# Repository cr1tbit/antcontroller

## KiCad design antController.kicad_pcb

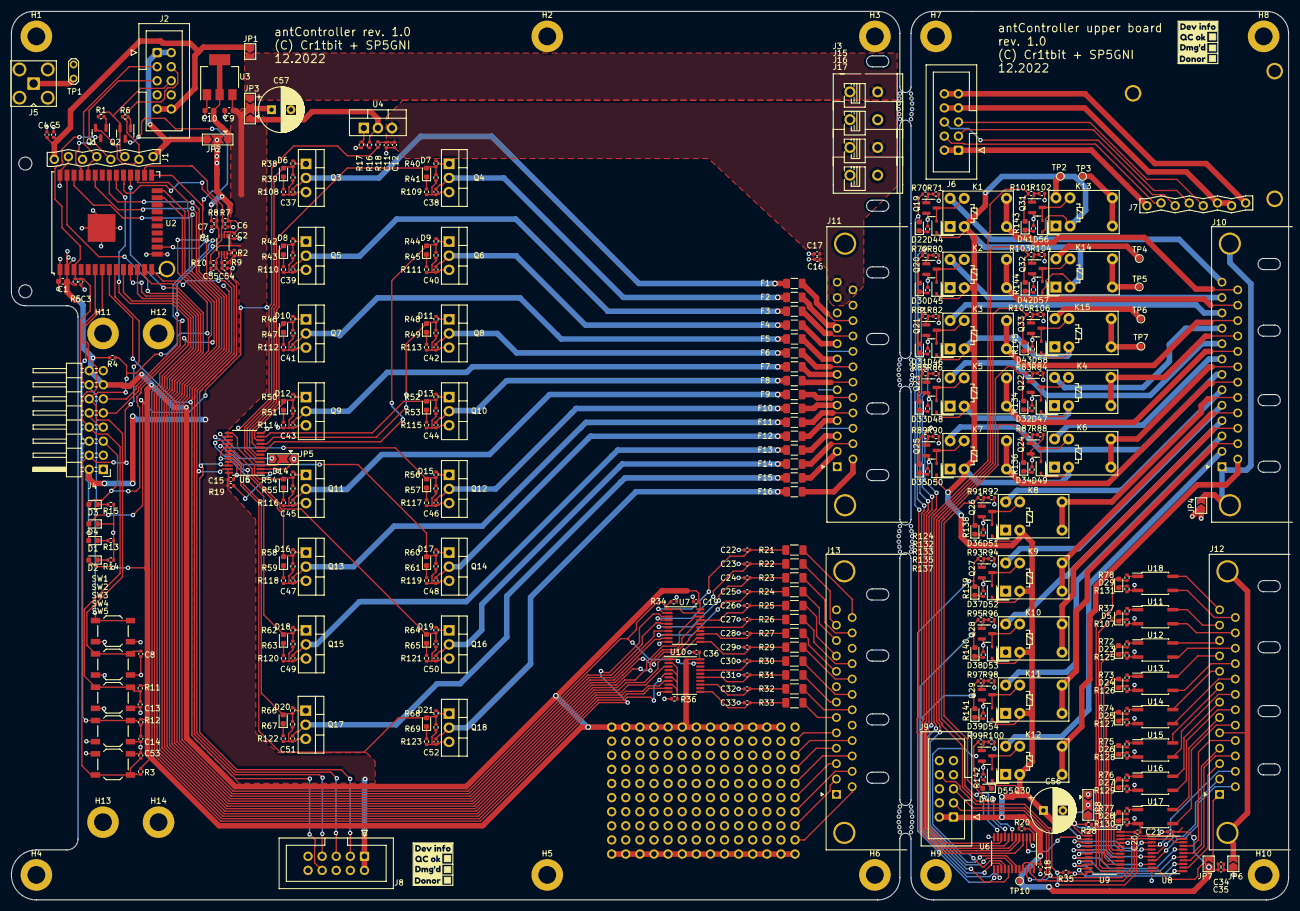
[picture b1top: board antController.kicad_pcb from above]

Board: 2 copper layers, 230.0 x 160.0 mm, 402 parts (0 on the bottom side), 326 nets.

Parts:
C1, C9, C10: 10u; C_0603_1608Metric
C2, C3, C4, C8, C11, C13, C14, C15, C16, C18, C19, C20, C21, C34, C36, C53: 100n; C_0402_1005Metric
C5, C12, C17, C35: 1n; C_0402_1005Metric
C6, C7, C54, C55: 1n/DNP; C_0402_1005Metric
C22, C23, C24, C25, C26, C27, C28, C29, C30, C31, C32, C33, C37, C38, C39, C40, C41, C42, C43, C44, C45, C46, C47, C48, C49, C50, C51, C52: 10n; C_0402_1005Metric
C56, C57: 220u; CP_Radial_D8.0mm_P3.50mm
D1, D2, D3, D4, D5, D6, D7, D8, D9, D10, D11, D12, D13, D14, D15, D16, D17, D18, D19, D20, D21, D22, D23, D24, D25, D26, D27, D28, D29, D30, D31, D32, D33, D34, D35, D36, D37, D38, D39, D40, D41, D42, D43: LED_RED; LED_0603_1608Metric
D44, D45, D46, D47, D48, D49, D50, D51, D52, D53, D54, D55, D56, D57, D58: 1N4148WS; D_SOD-323
F1, F2, F3, F4, F5, F6, F7, F8, F9, F10, F11, F12, F13, F14, F15, F16: FUSE_1206; Fuse_1206_3216Metric
H1, H2, H3, H4, H5, H6, H11, H12, H13, H14: SCRHOLE; MountingHole_3.2mm_M3_ISO7380_Pad
H7, H8, H9, H10: HOLE_B2; MountingHole_3.2mm_M3_ISO7380_Pad
J1, J7: Lichtenprog_conn; Lichtenprog_board
J2, J6, J8, J9: IDC10; IDC-Header_2x05_P2.54mm_Vertical
J3, J15, J16, J17: VIN; DG235-5.0
J4: FRONT_PANEL; PinHeader_2x08_P2.54mm_Horizontal
J5: SMA CONN; SMA_Amphenol_901-143_Horizontal
J10, J11, J12, J13: DB25_Male_MountingHoles; DSUB-25_Male_Horizontal_P2.77x2.84mm_EdgePinOffset9.90mm_Ho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
J14: Proto_matrix_14x10
JP1: 5V_PROG; SolderJumper-2_P1.3mm_Open_TrianglePad1.0x1.5mm
JP2: 3V3_SEL; SolderJumper-3_P2.0mm_Open_TrianglePad1.0x1.5mm
JP3: 5V_SEL; SolderJumper-3_P2.0mm_Open_TrianglePad1.0x1.5mm
JP4, JP6: GND_CONN; SolderJumper-2_P1.3mm_Open_TrianglePad1.0x1.5mm
JP5, JP8: IOEX_A2_SEL; SolderJumper-3_P2.0mm_Open_TrianglePad1.0x1.5mm
JP7: 5V_CONN; SolderJumper-2_P1.3mm_Open_TrianglePad1.0x1.5mm
K1, K2, K3, K4, K5, K6, K7, K8, K9, K10, K11, K12, K13, K14, K15: G5V-1; Relay_SPDT_Omron_G5V-1
Q1, Q2, Q19, Q20, Q21, Q22, Q23, Q24, Q25, Q26, Q27, Q28, Q29, Q30, Q31, Q32, Q33: MMBT3904; SOT-23
Q3, Q4, Q5, Q6, Q7, Q8, Q9, Q10, Q11, Q12, Q13, Q14, Q15, Q16, Q17, Q18: BUZ11; TO-220-3_Vertical
R1, R3, R4, R5, R6, R11, R12, R19, R20, R28, R34, R35, R36, R39, R41, R43, R45, R47, R49, R51, R53, R55, R57, R59, R61, R63, R65, R67, R69, R71, R80, R82, R84, R86, R88, R90, R92, R94, R96, R98, R100, R102, R104, R106: 10k; R_0402_1005Metric
R2: 200k; R_0402_1005Metric
R7, R8, R9, R10, R37, R38, R40, R42, R44, R46, R48, R50, R52, R54, R56, R58, R60, R62, R64, R66, R68, R70, R72, R73, R74, R75, R76, R77, R78, R79, R81, R83, R85, R87, R89, R91, R93, R95, R97, R99, R101, R103, R105: 4k7; R_0402_1005Metric
R13, R107, R108, R109, R110, R111, R112, R113, R114, R115, R116, R117, R118, R119, R120, R121, R122, R123, R124, R125, R126, R127, R128, R129, R130, R131, R132, R133, R134, R135, R136, R137, R138, R139, R140, R141, R142, R143, R144, R145: 33k; R_0402_1005Metric
R14, R15: 15k; R_0402_1005Metric
R16: 240; R_0402_1005Metric
R17: 720; R_0402_1005Metric
R18: 100k; R_0402_1005Metric
R21, R22, R23, R24, R25, R26, R27, R29, R30, R31, R32, R33: 10k_1206; R_1206_3216Metric_Pad1.30x1.75mm_HandSolder
SW1: B_RST; SW_SPST_TL3342
SW2: B1/BOOT; SW_SPST_TL3342
SW3: B2; SW_SPST_TL3342
SW4, SW5: B3; SW_SPST_TL3342
TP1: SMA PADS; TestPoint_2Pads_Pitch2.54mm_Drill0.8mm
TP2, TP3, TP4, TP5, TP6, TP7: RLPAD; TestPoint_Pad_D1.0mm
TP10: IOPAD; TestPoint_Pad_D1.0mm
U1: PCA9306DC; VSSOP-8_2.3x2mm_P0.5mm
U2: ESP32-WROOM-32U
U3: AZ1117-3.3; SOT-223-3_TabPin2
U4: LM317_TO-220; TO-220-3_Vertical
U5, U6, U9: PCA9555PW; TSSOP-24_4.4x7.8mm_P0.65mm
U7, U8, U10: 74HC244; TSSOP-20_4.4x6.5mm_P0.65mm
U11, U12, U13, U14, U15, U16, U17, U18: LTV-356T; SO-4_4.4x3.6mm_P2.54mm
kibuzzard-6394C46A, kibuzzard-6394C46A#2: G***; kibuzzard-6394C46A
kibuzzard-6394C47E, kibuzzard-6394C47E#2: G***; kibuzzard-6394C47E
kibuzzard-6394C445, kibuzzard-6394C445#2: G***; kibuzzard-6394C445
kibuzzard-6394C560, kibuzzard-6394C560#2: G***; kibuzzard-6394C560

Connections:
+3.3V: C1.1, C2.1, C19.1, C36.1, D2.2 (A), J4.13, J4.16, J14.A2, J14.A3, J14.A4, J14.A5, J14.A6, J14.A7, J14.A8, J14.A9, J14.A10, J14.A11, J14.A12, J14.A13, J14.A14, JP2.2 (C), R3.2, R4.2, R5.2, R7.2, R8.2, R11.2, R12.2, U1.2 (VREF1), U2.2 (VDD), U7.20 (VCC), U10.20 (VCC)
+5V: C9.1, C15.1, C57.1, D1.2 (A), J4.2, J8.1, J8.2, JP3.2 (C), JP5.3 (B), R2.2, R9.2, R10.2, R19.2, U3.3 (VI), U5.24 (VDD)
+5VD: C18.1, C20.1, C21.1, C34.2, C35.2, C56.1, D44.1 (K), D45.1 (K), D46.1 (K), D47.1 (K), D48.1 (K), D49.1 (K), D50.1 (K), D51.1 (K), D52.1 (K), D53.1 (K), D54.1 (K), D55.1 (K), D56.1 (K), D57.1 (K), D58.1 (K), J9.1, J9.2, JP7.1 (A), JP8.3 (B), K1.2, K2.2, K3.2, K4.2, K5.2, K6.2, K7.2, K8.2, K9.2, K10.2, K11.2, K12.2, K13.2, K14.2, K15.2, R20.2, R28.2, U6.21 (A0), U6.24 (VDD), U8.20 (VCC), U9.2 (A1), U9.24 (VDD)
+VDC: C11.1, C12.1, C16.1, C17.1, J11.12, J11.13, J11.25, J16.1, R18.2, U4.3 (VI)
/5V_IN: J3.1, JP1.2 (B), JP3.3 (B)
/B2: C13.1, J4.8, R11.1, SW3.2, U2.7 (IO35)
/B3: C14.1, J4.6, R12.1, SW4.2, U2.6 (IO34)
/B4: C53.1, J4.4, R3.1, SW5.2, U2.9 (IO33)
/Back connectors/B2_OUT_BUF_ENA: J9.8, R35.2, U8.1 (1OE), U8.19 (2OE)
/Back connectors/B2_PROG_RX: J6.5, J7.5 (PROG_TX)
/Back connectors/B2_PROG_TX: J6.3, J7.4 (PROG_RX)
/Back connectors/B2_SCL: J9.3, U6.23 (SDA), U9.23 (SDA)
/Back connectors/B2_SDA: J9.5, U6.22 (SCL), U9.22 (SCL)
/Back connectors/BUFF1: J12.17, U8.18 (1Y0)
/Back connectors/BUFF2: J12.4, U8.16 (1Y1)
/Back connectors/BUFF3: J12.16, U8.14 (1Y2)
/Back connectors/BUFF4: J12.3, U8.12 (1Y3)
/Back connectors/BUFF5: J12.15, U8.3 (2Y0)
/Back connectors/BUFF6: J12.2, U8.5 (2Y1)
/Back connectors/BUFF7: J12.14, U8.7 (2Y2)
/Back connectors/BUFF8: J12.1, JP7.2 (B), U8.9 (2Y3)
/Back connectors/G_SINK1: D6.2 (A), R38.2, R39.2, U5.4 (IO0_0)
/Back connectors/G_SINK2: D7.2 (A), R40.2, R41.2, U5.5 (IO0_1)
/Back connectors/G_SINK3: D8.2 (A), R42.2, R43.2, U5.6 (IO0_2)
/Back connectors/G_SINK4: D9.2 (A), R44.2, R45.2, U5.7 (IO0_3)
/Back connectors/G_SINK5: D10.2 (A), R46.2, R47.2, U5.8 (IO0_4)
/Back connectors/G_SINK6: D11.2 (A), R48.2, R49.2, U5.9 (IO0_5)
/Back connectors/G_SINK7: D12.2 (A), R50.2, R51.2, U5.10 (IO0_6)
/Back connectors/G_SINK8: D13.2 (A), R52.2, R53.2, U5.11 (IO0_7)
/Back connectors/G_SINK9: D14.2 (A), R54.2, R55.2, U5.13 (IO1_0)
/Back connectors/G_SINK10: D15.2 (A), R56.2, R57.2, U5.14 (IO1_1)
/Back connectors/G_SINK11: D16.2 (A), R58.2, R59.2, U5.15 (IO1_2)
/Back connectors/G_SINK12: D17.2 (A), R60.2, R61.2, U5.16 (IO1_3)
/Back connectors/G_SINK13: D18.2 (A), R62.2, R63.2, U5.17 (IO1_4)
/Back connectors/G_SINK14: D19.2 (A), R64.2, R65.2, U5.18 (IO1_5)
/Back connectors/G_SINK15: D20.2 (A), R66.2, R67.2, U5.19 (IO1_6)
/Back connectors/G_SINK16: D21.2 (A), R68.2, R69.2, U5.20 (IO1_7)
/Back connectors/OC1_A: D29.2 (A), R78.2, U9.13 (IO1_0)
/Back connectors/OC1_C: J12.13, U18.4
/Back connectors/OC1_E: J12.25, U18.3
/Back connectors/OC2_A: D5.2 (A), R37.2, U9.14 (IO1_1)
/Back connectors/OC2_C: J12.12, U11.4
/Back connectors/OC2_E: J12.24, U11.3
/Back connectors/OC3_A: D23.2 (A), R72.2, U9.15 (IO1_2)
/Back connectors/OC3_C: J12.11, U12.4
/Back connectors/OC3_E: J12.23, U12.3
/Back connectors/OC4_A: D24.2 (A), R73.2, U9.16 (IO1_3)
/Back connectors/OC4_C: J12.10, U13.4
/Back connectors/OC4_E: J12.22, U13.3
/Back connectors/OC5_A: D25.2 (A), R74.2, U9.17 (IO1_4)
/Back connectors/OC5_C: J12.9, U14.4
/Back connectors/OC5_E: J12.21, U14.3
/Back connectors/OC6_A: D26.2 (A), R75.2, U9.18 (IO1_5)
/Back connectors/OC6_C: J12.8, U15.4
/Back connectors/OC6_E: J12.20, U15.3
/Back connectors/OC7_A: D27.2 (A), R76.2, U9.19 (IO1_6)
/Back connectors/OC7_C: J12.7, U16.4
/Back connectors/OC7_E: J12.19, U16.3
/Back connectors/OC8_A: D28.2 (A), R77.2, U9.20 (IO1_7)
/Back connectors/OC8_C: J12.6, U17.4
/Back connectors/OC8_E: J12.18, U17.3
/Back connectors/RL1_A: J10.13, K1.10
/Back connectors/RL1_B: J10.25, K1.5, K1.6
/Back connectors/RL2_A: J10.12, K2.10
/Back connectors/RL2_B: J10.24, K2.5, K2.6
/Back connectors/RL3_A: J10.11, K3.10
/Back connectors/RL3_B: J10.23, K3.5, K3.6
/Back connectors/RL4_A: J10.10, K4.10
/Back connectors/RL4_B: J10.22, K4.5, K4.6
/Back connectors/RL5_A: J10.9, K5.10
/Back connectors/RL5_B: J10.21, K5.5, K5.6
/Back connectors/RL6_A: J10.8, K6.10
/Back connectors/RL6_B: J10.20, K6.5, K6.6
/Back connectors/RL7_A: J10.7, K7.10
/Back connectors/RL7_B: J10.19, K7.5, K7.6
/Back connectors/RL8_A: J10.6, K8.10
/Back connectors/RL8_B: J10.18, K8.5, K8.6
/Back connectors/RL9_A: J10.5, K9.10
/Back connectors/RL9_B: J10.17, K9.5, K9.6
/Back connectors/RL10_A: J10.4, K10.10
/Back connectors/RL10_B: J10.16, K10.5, K10.6
/Back connectors/RL11_A: J10.3, K11.10
/Back connectors/RL11_B: J10.15, K11.5, K11.6
/Back connectors/RL12_A: J10.2, K12.10
/Back connectors/RL12_B: J10.14, K12.5, K12.6
/Back connectors/RL13_A: K13.10, TP2.1
/Back connectors/RL13_B: K13.5, K13.6, TP3.1
/Back connectors/RL14_A: K14.10, TP4.1
/Back connectors/RL14_B: K14.5, K14.6, TP5.1
/Back connectors/RL15_A: K15.10, TP6.1
/Back connectors/RL15_B: K15.5, K15.6, TP7.1
/Back connectors/RL_CTRL1: D22.2 (A), R70.2, U6.4 (IO0_0)
/Back connectors/RL_CTRL2: D30.2 (A), R79.2, U6.5 (IO0_1)
/Back connectors/RL_CTRL3: D31.2 (A), R81.2, U6.6 (IO0_2)
/Back connectors/RL_CTRL4: D32.2 (A), R83.2, U6.7 (IO0_3)
/Back connectors/RL_CTRL5: D33.2 (A), R85.2, U6.8 (IO0_4)
/Back connectors/RL_CTRL6: D34.2 (A), R87.2, U6.9 (IO0_5)
/Back connectors/RL_CTRL7: D35.2 (A), R89.2, U6.10 (IO0_6)
/Back connectors/RL_CTRL8: D36.2 (A), R91.2, U6.11 (IO0_7)
/Back connectors/RL_CTRL9: D37.2 (A), R93.2, U6.13 (IO1_0)
/Back connectors/RL_CTRL10: D38.2 (A), R95.2, U6.14 (IO1_1)
/Back connectors/RL_CTRL11: D39.2 (A), R97.2, U6.15 (IO1_2)
/Back connectors/RL_CTRL12: D40.2 (A), R99.2, U6.16 (IO1_3)
/Back connectors/RL_CTRL13: D41.2 (A), R101.2, U6.17 (IO1_4)
/Back connectors/RL_CTRL14: D42.2 (A), R103.2, U6.18 (IO1_5)
/Back connectors/RL_CTRL15: D43.2 (A), R105.2, U6.19 (IO1_6)
/Back connectors/SINK1: C37.1, F1.1, Q3.2 (D)
/Back connectors/SINK2: C38.1, F2.1, Q4.2 (D)
/Back connectors/SINK3: C39.1, F3.1, Q5.2 (D)
/Back connectors/SINK4: C40.1, F4.1, Q6.2 (D)
/Back connectors/SINK5: C41.1, F5.1, Q7.2 (D)
/Back connectors/SINK6: C42.1, F6.1, Q8.2 (D)
/Back connectors/SINK7: C43.1, F7.1, Q9.2 (D)
/Back connectors/SINK8: C44.1, F8.1, Q10.2 (D)
/Back connectors/SINK9: C45.1, F9.1, Q11.2 (D)
/Back connectors/SINK10: C46.1, F10.1, Q12.2 (D)
/Back connectors/SINK11: C47.1, F11.1, Q13.2 (D)
/Back connectors/SINK12: C48.1, F12.1, Q14.2 (D)
/Back connectors/SINK13: C49.1, F13.1, Q15.2 (D)
/Back connectors/SINK14: C50.1, F14.1, Q16.2 (D)
/Back connectors/SINK15: C51.1, F15.1, Q17.2 (D)
/Back connectors/SINK16: C52.1, F16.1, Q18.2 (D)
/ESP_BOOT: C8.1, J4.12, Q2.3 (C), R4.1, SW2.2, U2.25 (IO0)
/ESP_EN: C3.1, J4.14, Q1.3 (C), R5.1, SW1.2, U2.3 (EN)
/I2C_RST: J8.7, U2.14 (IO12)
/IN_BUFF_ENA: R34.2, U2.16 (IO13), U7.1 (1OE), U7.19 (2OE), U10.1 (1OE), U10.19 (2OE)
/IO14: U2.13 (IO14), U7.18 (1Y0)
/IO15: U2.23 (IO15), U7.16 (1Y1)
/IO16: U2.27 (IO16), U7.14 (1Y2)
/IO17: U2.28 (IO17), U7.12 (1Y3)
/IO18: U2.30 (IO18), U7.3 (2Y0)
/IO19: U2.31 (IO19), U7.5 (2Y1)
/IO21: U2.33 (IO21), U7.7 (2Y2)
/IO22: U2.36 (IO22), U7.9 (2Y3)
/IO23: U2.37 (IO23), U10.3 (2Y0)
/IO25: U2.10 (IO25), U10.5 (2Y1)
/IO26: U2.11 (IO26), U10.7 (2Y2)
/IO27: U2.12 (IO27), U10.9 (2Y3)
/LED_STATUS: D3.2 (A), J4.5, U2.24 (IO2)
/OUT_BUF_ENA: J8.8, U2.8 (IO32)
/PROG_3V3: J1.1 (VDD), J2.1, J2.2, JP2.3 (B)
/PROG_5V: C4.1, C5.1, J1.8 (5V), J2.9, J2.10, JP1.1 (A)
/PROG_DTR: J1.3 (DTR), J2.6, Q2.2 (E), R1.1
/PROG_RTS: J1.2 (RTS), J2.4, Q1.2 (E), R6.1
/RXD: J1.5 (PROG_TX), J2.3, U2.34 (RXD0/IO3)
/SCL: C6.1, J4.11, R7.1, U1.3 (SCL1), U2.26 (IO4)
/SCL_5V: C54.1, J8.3, R9.1, U1.6 (SCL2), U5.22 (SCL)
/SDA: C7.1, J4.9, R8.1, U1.4 (SDA1), U2.29 (IO5)
/SDA_5V: C55.1, J8.5, R10.1, U1.5 (SDA2), U5.23 (SDA)
/TXD: J1.4 (PROG_RX), J2.5, U2.35 (TXD0/IO1)
GND: C1.2, C2.2, C3.2, C4.2, C5.2, C6.2, C7.2, C8.2, C9.2, C10.2, C11.2, C12.2, C13.2, C14.2, C15.2, C16.2, C17.2, C19.2, C22.2, C23.2, C24.2, C25.2, C26.2, C27.2, C28.2, C29.2, C30.2, C31.2, C32.2, C33.2, C36.2, C37.2, C38.2, C39.2, C40.2, C41.2, C42.2, C43.2, C44.2, C45.2, C46.2, C47.2, C48.2, C49.2, C50.2, C51.2, C52.2, C53.2, C54.2, C55.2, C57.2, D4.1 (K), H1.1, H2.1, H3.1, H4.1, H5.1, H6.1, H11.1, H12.1, H13.1, H14.1, J1.6 (GND), J1.7 (GND), J2.7, J2.8, J4.7, J4.10, J4.15, J5.2 (Ext), J8.9, J8.10, J11.0 (PAD), J11.1, J11.6, J11.11, J11.16, J11.21, J11.24, J13.0 (PAD), J13.1, J13.8, J13.13, J13.18, J13.23, J14.A1, J14.J1, J14.J2, J14.J3, J14.J4, J14.J5, J14.J6, J14.J7, J14.J8, J14.J9, J14.J10, J14.J11, J14.J12, J14.J13, J14.J14, J15.1, J17.1, JP5.1 (A), Q3.3 (S), Q4.3 (S), Q5.3 (S), Q6.3 (S), Q7.3 (S), Q8.3 (S), Q9.3 (S), Q10.3 (S), Q11.3 (S), Q12.3 (S), Q13.3 (S), Q14.3 (S), Q15.3 (S), Q16.3 (S), Q17.3 (S), Q18.3 (S), R13.1, R14.1, R15.1, R17.1, R34.1, R36.1, R39.1, R41.1, R43.1, R45.1, R47.1, R49.1, R51.1, R53.1, R55.1, R57.1, R59.1, R61.1, R63.1, R65.1, R67.1, R69.1, R108.1, R109.1, R110.1, R111.1, R112.1, R113.1, R114.1, R115.1, R116.1, R117.1, R118.1, R119.1, R120.1, R121.1, R122.1, R123.1, SW1.1, SW2.1, SW3.1, SW4.1, SW5.1, TP1.1, U1.1 (GND), U2.1 (GND), U2.15 (GND), U2.38 (GND), U2.39 (GND), U3.1 (GND), U5.2 (A1), U5.12 (VSS), U5.21 (A0), U7.10 (GND), U10.10 (GND)
GND2: C18.2, C20.2, C21.2, C34.1, C35.1, C56.2, H7.1, H8.1, H9.1, H10.1, J9.9, J9.10, JP4.1 (A), JP6.1 (A), JP8.1 (A), Q19.2 (E), Q20.2 (E), Q21.2 (E), Q22.2 (E), Q23.2 (E), Q24.2 (E), Q25.2 (E), Q26.2 (E), Q27.2 (E), Q28.2 (E), Q29.2 (E), Q30.2 (E), Q31.2 (E), Q32.2 (E), Q33.2 (E), R35.1, R71.1, R80.1, R82.1, R84.1, R86.1, R88.1, R90.1, R92.1, R94.1, R96.1, R98.1, R100.1, R102.1, R104.1, R106.1, R107.1, R124.1, R125.1, R126.1, R127.1, R128.1, R129.1, R130.1, R131.1, R132.1, R133.1, R134.1, R135.1, R136.1, R137.1, R138.1, R139.1, R140.1, R141.1, R142.1, R143.1, R144.1, R145.1, U6.2 (A1), U6.12 (VSS), U8.10 (GND), U9.12 (VSS), U9.21 (A0), U11.2, U12.2, U13.2, U14.2, U15.2, U16.2, U17.2, U18.2
unnamed: C10.1, JP2.1 (A), U3.2 (VO)
unnamed: C22.1, R21.2, U7.2 (1A0)
unnamed: C23.1, R22.2, U7.4 (1A1)
unnamed: C24.1, R23.2, U7.6 (1A2)
unnamed: C25.1, R24.2, U7.8 (1A3)
unnamed: C26.1, R25.2, U7.17 (2A0)
unnamed: C27.1, R26.2, U7.15 (2A1)
unnamed: C28.1, R27.2, U7.13 (2A2)
unnamed: C29.1, R29.2, U7.11 (2A3)
unnamed: C30.1, R30.2, U10.17 (2A0)
unnamed: C31.1, R31.2, U10.15 (2A1)
unnamed: C32.1, R32.2, U10.13 (2A2)
unnamed: C33.1, R33.2, U10.11 (2A3)
unnamed: D1.1 (K), R13.2
unnamed: D2.1 (K), R14.2
unnamed: D3.1 (K), R15.2
unnamed: D4.2 (A), R18.1
unnamed: D5.1 (K), R107.2
unnamed: D6.1 (K), R108.2
unnamed: D7.1 (K), R109.2
unnamed: D8.1 (K), R110.2
unnamed: D9.1 (K), R111.2
unnamed: D10.1 (K), R112.2
unnamed: D11.1 (K), R113.2
unnamed: D12.1 (K), R114.2
unnamed: D13.1 (K), R115.2
unnamed: D14.1 (K), R116.2
unnamed: D15.1 (K), R117.2
unnamed: D16.1 (K), R118.2
unnamed: D17.1 (K), R119.2
unnamed: D18.1 (K), R120.2
unnamed: D19.1 (K), R121.2
unnamed: D20.1 (K), R122.2
unnamed: D21.1 (K), R123.2
unnamed: D22.1 (K), R124.2
unnamed: D23.1 (K), R125.2
unnamed: D24.1 (K), R126.2
unnamed: D25.1 (K), R127.2
unnamed: D26.1 (K), R128.2
unnamed: D27.1 (K), R129.2
unnamed: D28.1 (K), R130.2
unnamed: D29.1 (K), R131.2
unnamed: D30.1 (K), R132.2
unnamed: D31.1 (K), R133.2
unnamed: D32.1 (K), R134.2
unnamed: D33.1 (K), R135.2
unnamed: D34.1 (K), R136.2
unnamed: D35.1 (K), R137.2
unnamed: D36.1 (K), R138.2
unnamed: D37.1 (K), R139.2
unnamed: D38.1 (K), R140.2
unnamed: D39.1 (K), R141.2
unnamed: D40.1 (K), R142.2
unnamed: D41.1 (K), R143.2
unnamed: D42.1 (K), R144.2
unnamed: D43.1 (K), R145.2
unnamed: D44.2 (A), K1.9, Q19.3 (C)
unnamed: D45.2 (A), K2.9, Q20.3 (C)
unnamed: D46.2 (A), K3.9, Q21.3 (C)
unnamed: D47.2 (A), K4.9, Q22.3 (C)
unnamed: D48.2 (A), K5.9, Q23.3 (C)
unnamed: D49.2 (A), K6.9, Q24.3 (C)
unnamed: D50.2 (A), K7.9, Q25.3 (C)
unnamed: D51.2 (A), K8.9, Q26.3 (C)
unnamed: D52.2 (A), K9.9, Q27.3 (C)
unnamed: D53.2 (A), K10.9, Q28.3 (C)
unnamed: D54.2 (A), K11.9, Q29.3 (C)
unnamed: D55.2 (A), K12.9, Q30.3 (C)
unnamed: D56.2 (A), K13.9, Q31.3 (C)
unnamed: D57.2 (A), K14.9, Q32.3 (C)
unnamed: D58.2 (A), K15.9, Q33.3 (C)
unnamed: F1.2, J11.23
unnamed: F2.2, J11.10
unnamed: F3.2, J11.22
unnamed: F4.2, J11.9
unnamed: F5.2, J11.8
unnamed: F6.2, J11.20
unnamed: F7.2, J11.7
unnamed: F8.2, J11.19
unnamed: F9.2, J11.18
unnamed: F10.2, J11.5
unnamed: F11.2, J11.17
unnamed: F12.2, J11.4
unnamed: F13.2, J11.3
unnamed: F14.2, J11.15
unnamed: F15.2, J11.2
unnamed: F16.2, J11.14
unnamed: J5.1 (In), TP1.2
unnamed: J6.1, J6.2, J7.1 (VDD)
unnamed: J6.4, J7.2 (RTS)
unnamed: J6.6, J7.3 (DTR)
unnamed: J6.7, J6.8, J7.6 (GND), J7.7 (GND)
unnamed: J6.9, J6.10, J7.8 (5V)
unnamed: J10.0 (PAD), J10.1, JP4.2 (B)
unnamed: J12.0 (PAD), J12.5, JP6.2 (B)
unnamed: J13.2, J14.H1
unnamed: J13.3, J14.F1
unnamed: J13.4, J14.D1
unnamed: J13.5, J14.B1
unnamed: J13.6, R33.1
unnamed: J13.7, R31.1
unnamed: J13.9, R27.1
unnamed: J13.10, R25.1
unnamed: J13.11, R24.1
unnamed: J13.12, R22.1
unnamed: J13.14, J14.I1
unnamed: J13.15, J14.G1
unnamed: J13.16, J14.E1
unnamed: J13.17, J14.C1
unnamed: J13.19, R32.1
unnamed: J13.20, R30.1
unnamed: J13.21, R29.1
unnamed: J13.22, R26.1
unnamed: J13.24, R23.1
unnamed: J13.25, R21.1
unnamed: JP3.1 (A), R16.1, U4.2 (VO)
unnamed: JP5.2 (C), U5.3 (A2)
unnamed: JP8.2 (C), U6.3 (A2), U9.3 (A2)
unnamed: Q1.1 (B), R1.2
unnamed: Q2.1 (B), R6.2
unnamed: Q3.1 (G), R38.1
unnamed: Q4.1 (G), R40.1
unnamed: Q5.1 (G), R42.1
unnamed: Q6.1 (G), R44.1
unnamed: Q7.1 (G), R46.1
unnamed: Q8.1 (G), R48.1
unnamed: Q9.1 (G), R50.1
unnamed: Q10.1 (G), R52.1
unnamed: Q11.1 (G), R54.1
unnamed: Q12.1 (G), R56.1
unnamed: Q13.1 (G), R58.1
unnamed: Q14.1 (G), R60.1
unnamed: Q15.1 (G), R62.1
unnamed: Q16.1 (G), R64.1
unnamed: Q17.1 (G), R66.1
unnamed: Q18.1 (G), R68.1
unnamed: Q19.1 (B), R70.1, R71.2
unnamed: Q20.1 (B), R79.1, R80.2
unnamed: Q21.1 (B), R81.1, R82.2
unnamed: Q22.1 (B), R83.1, R84.2
unnamed: Q23.1 (B), R85.1, R86.2
unnamed: Q24.1 (B), R87.1, R88.2
unnamed: Q25.1 (B), R89.1, R90.2
unnamed: Q26.1 (B), R91.1, R92.2
unnamed: Q27.1 (B), R93.1, R94.2
unnamed: Q28.1 (B), R95.1, R96.2
unnamed: Q29.1 (B), R97.1, R98.2
unnamed: Q30.1 (B), R99.1, R100.2
unnamed: Q31.1 (B), R101.1, R102.2
unnamed: Q32.1 (B), R103.1, R104.2
unnamed: Q33.1 (B), R105.1, R106.2
unnamed: R2.1, U1.7 (VREF2), U1.8 (EN)
unnamed: R16.2, R17.2, U4.1 (ADJ)
unnamed: R19.1, U5.1 (~INT)
unnamed: R20.1, U6.1 (~INT)
unnamed: R28.1, U9.1 (~INT)
unnamed: R36.2, U10.2 (1A0), U10.4 (1A1), U10.6 (1A2), U10.8 (1A3)
unnamed: R37.1, U11.1
unnamed: R72.1, U12.1
unnamed: R73.1, U13.1
unnamed: R74.1, U14.1
unnamed: R75.1, U15.1
unnamed: R76.1, U16.1
unnamed: R77.1, U17.1
unnamed: R78.1, U18.1
unnamed: TP10.1, U6.20 (IO1_7)
unnamed: U8.2 (1A0), U9.4 (IO0_0)
unnamed: U8.4 (1A1), U9.5 (IO0_1)
unnamed: U8.6 (1A2), U9.6 (IO0_2)
unnamed: U8.8 (1A3), U9.7 (IO0_3)
unnamed: U8.11 (2A3), U9.11 (IO0_7)
unnamed: U8.13 (2A2), U9.10 (IO0_6)
unnamed: U8.15 (2A1), U9.9 (IO0_5)
unnamed: U8.17 (2A0), U9.8 (IO0_4)

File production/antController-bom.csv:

Comment,Designator,Footprint,LCSC,mouser,MPN,MANU,checked
10u,"C1,C9,C10",Capacitor_SMD:C_0603_1608Metric,C15525,,,,
100n,"C2,C3,C4,C8,C11,C13,C14,C15,C16,C18,C19,C20,C21,C34,C36,C53",Capacitor_SMD:C_0402_1005Metric,C1525,,,,
10n,"C22,C23,C24,C25,C26,C27,C28,C29,C30,C31,C32,C33,C37,C38,C39,C40,C41,C42,C43,C44,C45,C46,C47,C48,C49,C50,C51,C52",Capacitor_SMD:C_0402_1005Metric,C15195,,,,
1n,"C5,C12,C17,C35",Capacitor_SMD:C_0402_1005Metric,C46653,,,,
1n/DNP,"C6,C7,C54,C55",Capacitor_SMD:C_0402_1005Metric,,,,,
LED_RED,"D1,D2,D3,D4,D5,D6,D7,D8,D9,D10,D11,D12,D13,D14,D15,D16,D17,D18,D19,D20,D21,D22,D23,D24,D25,D26,D27,D28,D29,D30,D31,D32,D33,D34,D35,D36,D37,D38,D39,D40,D41,D42,D43",LED_SMD:LED_0603_1608Metric,C2286,,,,
1N4148WS,"D44,D45,D46,D47,D48,D49,D50,D51,D52,D53,D54,D55,D56,D57,D58",Diode_SMD:D_SOD-323,C2128,,,,
FUSE_1206,"F1,F2,F3,F4,F5,F6,F7,F8,F9,F10,F11,F12,F13,F14,F15,F16",Fuse:Fuse_1206_3216Metric,C183160,,,,
SCRHOLE,"H1,H2,H3,H4,H5,H6,H11,H12,H13,H14",MountingHole:MountingHole_3.2mm_M3_ISO7380_Pad,,,,,
MMBT3904,"Q1,Q2,Q19,Q20,Q21,Q22,Q23,Q24,Q25,Q26,Q27,Q28,Q29,Q30,Q31,Q32,Q33",Package_TO_SOT_SMD:SOT-23,C20526,,,,
10k,"R1,R3,R4,R5,R6,R11,R12,R19,R20,R28,R34,R35,R36,R39,R41,R43,R45,R47,R49,R51,R53,R55,R57,R59,R61,R63,R65,R67,R69,R71,R80,R82,R84,R86,R88,R90,R92,R94,R96,R98,R100,R102,R104,R106",Resistor_SMD:R_0402_1005Metric,C25744,,,,
33k,"R13,R107,R108,R109,R110,R111,R112,R113,R114,R115,R116,R117,R118,R119,R120,R121,R122,R123,R124,R125,R126,R127,R128,R129,R130,R131,R132,R133,R134,R135,R136,R137,R138,R139,R140,R141,R142,R143,R144,R145",Resistor_SMD:R_0402_1005Metric,C25779,,,,
15k,"R14,R15",Resistor_SMD:R_0402_1005Metric,0402,,,,
240,R16,Resistor_SMD:R_0402_1005Metric,C114755,,,,
720,R17,Resistor_SMD:R_0402_1005Metric,C137941,,,,
100k,R18,Resistor_SMD:R_0402_1005Metric,C25741,,,,
200k,R2,Resistor_SMD:R_0402_1005Metric,C25764,,,,
10k_1206,"R21,R22,R23,R24,R25,R26,R27,R29,R30,R31,R32,R33",Resistor_SMD:R_1206,C17902,,,,
4k7,"R7,R8,R9,R10,R37,R38,R40,R42,R44,R46,R48,R50,R52,R54,R56,R58,R60,R62,R64,R66,R68,R70,R72,R73,R74,R75,R76,R77,R78,R79,R81,R83,R85,R87,R89,R91,R93,R95,R97,R99,R101,R103,R105",Resistor_SMD:R_0402_1005Metric,C25900,,,,
B_RST,SW1,Button_Switch_SMD:SW_SPST_TL3342,C318884,,,,
B1/BOOT,SW2,Button_Switch_SMD:SW_SPST_TL3342,C318884,,,,
B2,SW3,Button_Switch_SMD:SW_SPST_TL3342,C318884,,,,
B3,"SW4,SW5",Button_Switch_SMD:SW_SPST_TL3342,C318884,,,,
PCA9306DC,U1,Package_SO:VSSOP-8_2.3x2mm_P0.5mm,C33196,,,,
LTV-356T,"U11,U12,U13,U14,U15,U16,U17,U18",Package_SO:SO-4_4.4x3.6mm_P2.54mm,C115452,,,,
AZ1117-3.3,U3,Package_TO_SOT_SMD:SOT-223-3_TabPin2,C6186,,,,
PCA9555PW,"U5,U6,U9",Package_SO:TSSOP-24_4.4x7.8mm_P0.65mm,C128392,,,,
74HC244,"U7,U8,U10",Package_SO:TSSOP-20_4.4x6.5mm_P0.65mm,C6835,,,,

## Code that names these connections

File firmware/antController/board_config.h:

#pragma once 

const int PIN_I2C_SCL = 4;
const int PIN_I2C_SDA = 5;
const int PIN_I2C_RST = 12;

// board inputs

const uint8_t PIN_INPUT_1 = 14;
const uint8_t PIN_INPUT_2 = 15;
const uint8_t PIN_INPUT_3 = 16;
const uint8_t PIN_INPUT_4 = 17;

const uint8_t PIN_INPUT_5 = 18;
const uint8_t PIN_INPUT_6 = 19;
const uint8_t PIN_INPUT_7 = 21;
const uint8_t PIN_INPUT_8 = 22;

const uint8_t PIN_INPUT_9 = 23;
const uint8_t PIN_INPUT_10 = 25;
const uint8_t PIN_INPUT_11 = 26;
const uint8_t PIN_INPUT_12 = 27;

const uint8_t PIN_IN_BUFF_ENA = 13;


const uint8_t input_pins_array[] = {
  PIN_INPUT_1,
  PIN_INPUT_2,
  PIN_INPUT_3,
  PIN_INPUT_4,
  PIN_INPUT_5,
  PIN_INPUT_6,
  PIN_INPUT_7,
  PIN_INPUT_8,
  PIN_INPUT_9,
  PIN_INPUT_10,
  PIN_INPUT_11,
  PIN_INPUT_12
};

const int input_pins_array_len = sizeof(input_pins_array)/sizeof(input_pins_array[0]);

// user interface
const int PIN_BOOT_BUT1 = 0;
const int PIN_BUT2 = 33;
const int PIN_BUT3 = 34;
const int PIN_BUT4 = 35;

const int PIN_LED_STATUS = 2;



// trash

/*
for (size_t i = 0; i < 16; ++i) {
    Serial.print("set port high: ");
    Serial.println(i);

    exp_mosfets.write((PCA95x5::Port::Port)i, PCA95x5::Level::H);
    exp_relays.write((PCA95x5::Port::Port)i, PCA95x5::Level::H);
    exp_opto_io.write((PCA95x5::Port::Port)i, PCA95x5::Level::H);
    // Serial.println(ioex.read(), BIN);
    delay(500);
  }

  for (size_t i = 0; i < 16; ++i) {
    Serial.print("set port low: ");
    Serial.println(i);

    exp_mosfets.write((PCA95x5::Port::Port)i, PCA95x5::Level::L);
    exp_relays.write((PCA95x5::Port::Port)i, PCA95x5::Level::L);
    exp_opto_io.write((PCA95x5::Port::Port)i, PCA95x5::Level::L);

    // Serial.println(ioex.read(), BIN);
    delay(500);
  }


typedef {
  int esp_pin_num;
  uint32_t pin_bitmask;
  bool is_enabled;
  const char[20] name_verbose;
} board_input_t;


*/

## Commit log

2022-11-04 add files
2022-11-06 work on schematic
2022-12-05 finish schematic, work on layout
2022-12-06 routing mostly done, fixing schematic issues
2022-12-06 succesfully run replicate layout on relays
2022-12-11 finish routing and silk
2022-12-12 prod files
2022-12-26 add firmware stub
2022-12-27 work on firmware, add an example website from another project
2022-12-30 add library for controling device IO
2022-12-31 PoC API call for IO
2023-01-05 define output API, fun with littleFS and SPIFFSEditor
2023-01-06 apply singleton pattern to ioController, POC event sender, input API
2023-03-15 move to platformio
2023-03-15 gitignoring
2023-03-24 repo cleanup
2023-05-03 add shit
2023-05-21 rewrite api in beautiful C++ *o*
2023-05-23 fix pin numeration
2023-06-04 deal with ranges
2023-06-23 fix errors in bits commands
2023-08-08 move to new logging lib, add display support, add serial console
2023-08-11 move FW to separate repo
2023-08-21 from future import missing resistors
